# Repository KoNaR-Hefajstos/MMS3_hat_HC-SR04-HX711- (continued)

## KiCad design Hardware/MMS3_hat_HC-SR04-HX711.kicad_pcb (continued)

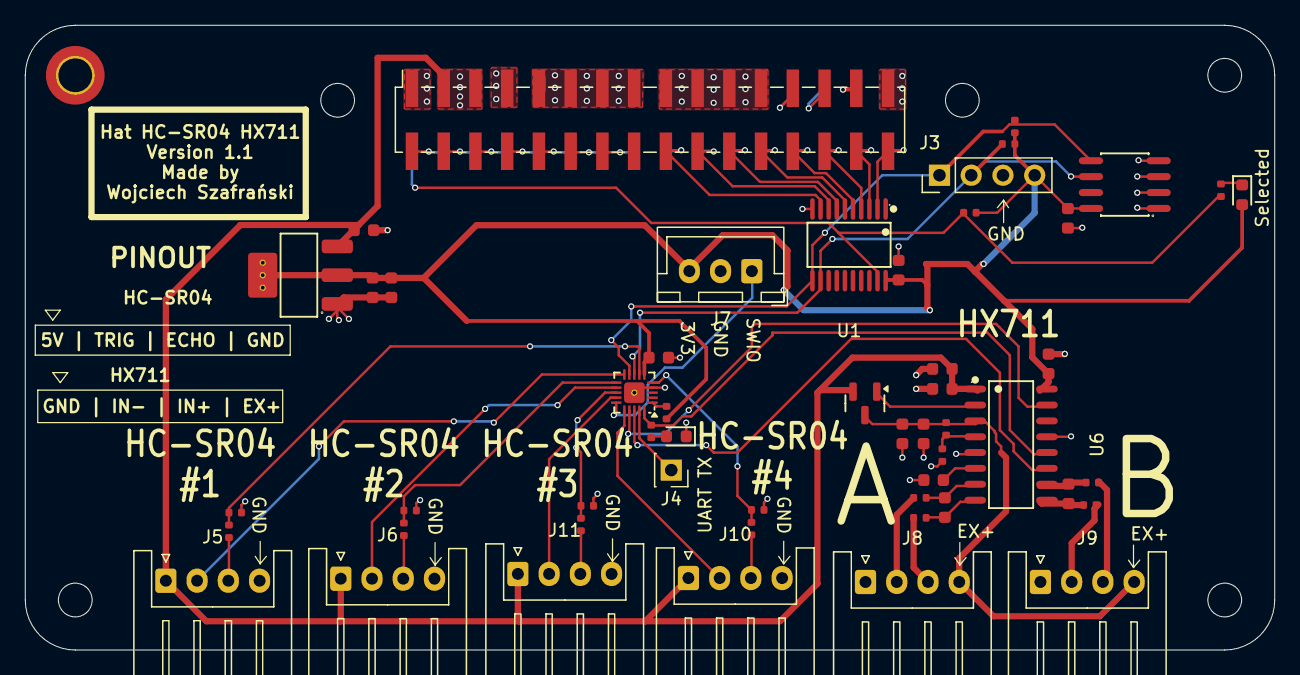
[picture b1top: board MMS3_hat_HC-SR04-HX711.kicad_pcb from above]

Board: 2 copper layers, 100.0 x 50.0 mm, 59 parts (1 on the bottom side), 57 nets.

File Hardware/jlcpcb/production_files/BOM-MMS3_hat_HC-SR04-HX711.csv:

Comment,Designator,Footprint,LCSC,Quantity
100nF,"C1,C10,C12,C13,C15,C16,C2,C6,C9",C_0603,C14663,9
100Ω,"R13,R14,R15,R16",R_0402,C25076,4
10kΩ,"R1,R11,R19,R21,R25,R5,R7,R9",R_0402,C25744,8
10uF,"C11,C14,C3,C4,C5",C_0603,C19702,5
15kΩ,"R20,R22,R6,R8",R_0402,C25756,4
20kΩ,R23,R_0402,C25765,1
330Ω,"R12,R27",R_0402,C25104,2
8.2kΩ,R24,R_0402,C25924,1
AMS1117,U3,SOT-223-3_L6.5-W3.4-P2.30-LS7.0-BR,C6186,1
CH32V003F4U6,U5,QFN-20-1EP_3x3mm_P0.4mm_EP1.65x1.65mm,C5299908,1
HX711_C6705483,U6,SOP-16_L10.0-W3.9-P1.27-LS6.0-BL,C6705483,1
M24C64,U2,SOIC-8_L5.0-W4.0-P1.27-LS6.0-BL,C79988,1
MMBT3906,Q3,Q_SOT-23,C7420354,1
Red,"D3,D4",D_0603,C2286,2
SN74CB3Q3245PWR,U1,TSSOP-20_L6.5-W4.4-P0.65-LS6.4-BL,C470961,1
Conn_01x04_Pin,J8,JST_XH_S4B-XH-A_1x04_P2.50mm_Horizontal,,1
Debug_USART_TX,J4,PinSocket_1x01_P2.54mm_Vertical,,1
Chainbus Out,J2,PinSocket_2x16_P2.54mm_Vertical_SMD,,1
Conn_01x04_Pin,J3,PinHeader_1x04_P2.54mm_Vertical,,1
Conn_01x04_Pin,J11,JST_XH_S4B-XH-A_1x04_P2.50mm_Horizontal,,1
Conn_01x04_Pin,J10,JST_XH_S4B-XH-A_1x04_P2.50mm_Horizontal,,1
Conn_01x04_Pin,J9,JST_XH_S4B-XH-A_1x04_P2.50mm_Horizontal,,1
Program,J7,JST_XH_B3B-XH-A_1x03_P2.50mm_Vertical,,1
Conn_01x04_Pin,J5,JST_XH_S4B-XH-A_1x04_P2.50mm_Horizontal,,1
Conn_01x04_Pin,J6,JST_XH_S4B-XH-A_1x04_P2.50mm_Horizontal,,1
Chainbus in,J1,PinHeader_2x16_P2.54mm_Vertical_SMD,,1

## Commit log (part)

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2026-03-01 finished schematic
2026-03-01 finished routing and exported gerber
2026-03-09 added readme
2026-04-08 updated bus switch to sensible one
2026-04-08 rounded da corners
2026-04-11 Added version number
2026-04-18 fixed selected led polarity
2026-04-18 made pinout on silkscreen nicer
2026-04-20 generated final gerber
2026-06-08 BREAKING: updated CH32 programming pinout
2026-06-10 added documentation
